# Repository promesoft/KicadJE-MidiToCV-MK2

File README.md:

# Kicad-MidiToCV
Midi to CV in Eurorack 

# MK2 Design 
## Status - PCB delivered tested
## Initial 
| Stage  | Detail | Status |
| ------------- | ------------- | ------------- |
| create material  | sch/pcb | produced MK2 Rev A  |
| | gerber | Produced MK2 |
| production  | ordered  |  |
|  | produced | yes |
|  | delivered | yes |
## Preliminary validation
| Test  | Detail | Status |
| ------------- | ------------- | ------------- |
| Initial Inspection | conflict between LED on front panel and optional CV7 | OK |
| Initial Technical Test |   | OK |
| Initial Product Test |  | OK! |
|  | LED's | OK |
|  | Encoder | OK |
|  | CV1+CV2 | OK |
|  | GATE 1,2,3,4 | OK |
|  | MIDI I/O | OK |

## Secondary validation
| Test  | Detail | Status |
| ------------- | ------------- |------------- |
| Product Test |  | |
| Quality |  | |
| Long Term Product Test | | Mounted in rack |

## Software 
| Test  | Detail | Status |
| ------------- | ------------- |------------- |
| Initial SW | copy from MK1 and adjusted | OK! |
| MIDI I/O | UI | |
| MIDI I/O | Filtering and change ch | |
| CV Control | UI |  |
| CV Control | |  |
| LFO Control | UI |  |
| LFO Control | Function |  |

## Errata
 * Physical mounting of the faceplate to holes on the base plate requires other dimensions of the angled mounts. The mounts can be very difficult to get in place due to limited space behind the front PCB.
## Issues and Notes
 * Note - the 4 value LED's are routed across the front board next to analogue and gate signals - so care should be taken when deciding between constant power or PWM control of brightness. The other LED's are not considered as vital as they will normally be lit when config is changed.
 * Consider replacing single row board connector with double row.
 * Physical construction not finalized
### Workarounds

## Base Construction
### Arduino base board 
 - Arduino Nano
 - MIDI IN/OUT connectors
 - CV 1 and CV 2 as Mini Jacks (PJ-301) with variable x2-x3 amplification and 1st order LP filter
 - Gate 1 and Gate 2 as Mini Jacks (PJ-301) 5V
 - Gate 3 and Gate 4 as Mini Jacks (PJ-321) with fixed x2 amplification and sallen-key LP 2nd order filter
 - Board connector 9pin and 11pin from base board to front board
 - 16pin Europower connector
 - Barreljack for 7-12V digital Pwr

## Vital Components
 - Arduino Nano - where the magic lives (remember to socket it to be able to reprogram it - two jumpers are in place for Rx/Tx so socket may be avoided)
 - Jack connectors: PJ-321 for the base board and PJ-301 for the front board (important for the footprint)
 - ALPS EC-11 Encoder (important for the footprint and 3D alignment)
 - ALPS RV09 horisontal potentiometer (important for the footprint and for variable CV out - can be omitted if this is not needed)
 - MCP4825 module - if chosen (important for CV out function - footprint needs to match)
 - TL072 or similar dual op amp
 
### Mechanical

The construction is still split in two - but the MK2 design relies on a base board that is 90degrees to the face plate (like the MK1) and a connector board that is 10mm behind the faceplate 90 degrees angle to the base board.

.png)
-----------------------------------------------------

# MK1 Design
## Status - Rev B - Ongoing PCB layout and Sch update

## Status - Rev A Mounted - Midi code in progress
### Issues and Notes
Please note that the PIN1 and PIN2 are GATE. This is note described clearly in http://www.doepfer.de/a100_man/a100t_e.htm and needs to be noted when soldering the IDC header or when cabling if a Pin header has been mounted.
 * The two pots on the breakout board are too close for adding a knob
 * The orientation of the pinheader for the MCP4725 module - if mounted incorrectly the magic smoke disappears
 * 0R could be replaced with SMD jumpers
 * Consider a 200 mA fuse for Vin and 50mA for +5V pwr
 * The mounting hole that is off center is not matching both boards
### Errata
 * Footprint of PJ-321 has too small drill holes (1mm) - major
 * Footprint of PJ-321 is too narrow in the rear end :) - minor issue
 * Midi out circuit is WRONG - Major
### Workarounds
* Midi out not working - PCB workaround mod partially possible  
 * --Remove GND around DIN pin 5 (bottom copper side)
 * --Cut GND track to DIN pin 5 (top copper side)
 * --Remove Q1, R6, R9
 * --Connect 220R THT to base pad on Q1
 * --Connect C and E on Q1
 * --Add GND wire to pin2 of MIDI out DIN
## Physical Construction
 - 100x100mm
 - Separate unit with no alteration
 - Optional split in 2 for eurorack mount mirrored config

## Vital Components
 - Arduino Nano - where the magic lives (remember to socket it to be able to reprogram it)
 - Jack connectors: PJ-321 (important for the footprint)
 - KY-40 Encoder module (important for the pullup, footprint and 3D alignment)
 - MCP4825 module - if chosen (important for CV out function - footprint needs to match)
 If these are chosen the last two CV jacks should be ommitted.
 - MCP4728 chip - if chosen (important for the last 2 CV out)

## MIDI Board Features
### Single board - MIDI I/O and MIDI to CV
The board can be used as is for a prototype development of MIDI to CV
### Split board Eurorack - MIDI I/O and MIDI to CV
The board can be devided in two and combined front to front with spacers for a MIDI to CV eurorack module.
### Base board Eurorack - MIDI I/O
If only MIDI features are required the base board can work without the IO section.

## Generic Board Features
### Split board Options
The main board (with the arduino) has a couple of headers that can be connected to a different interface board using I2C, Analogue Inputs and Digital I/O.
### Non MIDI board
The MIDI components can be omitted if the features does not require MIDI, like an LFO, VCO or ADSR circuit.

## Base Construction
Arduino Nano based Controller and MIDI decoder.

### MIDI In
MIDI In through a PC814 (or optional PC817) Optocoupler and into the RX pin on the Arduino

### Midi Out
Optional expansion

### Gate
Gate pins from Arduino

## CV Out
I2C Dac with 2 options
### I2C Dac - Option 1 - Two Single channel DAC
2x MCP4725 DAC 
### I2C Dac - Option 2 - One 4 channel DAC
1x MCP4728

# RevB

# RevA

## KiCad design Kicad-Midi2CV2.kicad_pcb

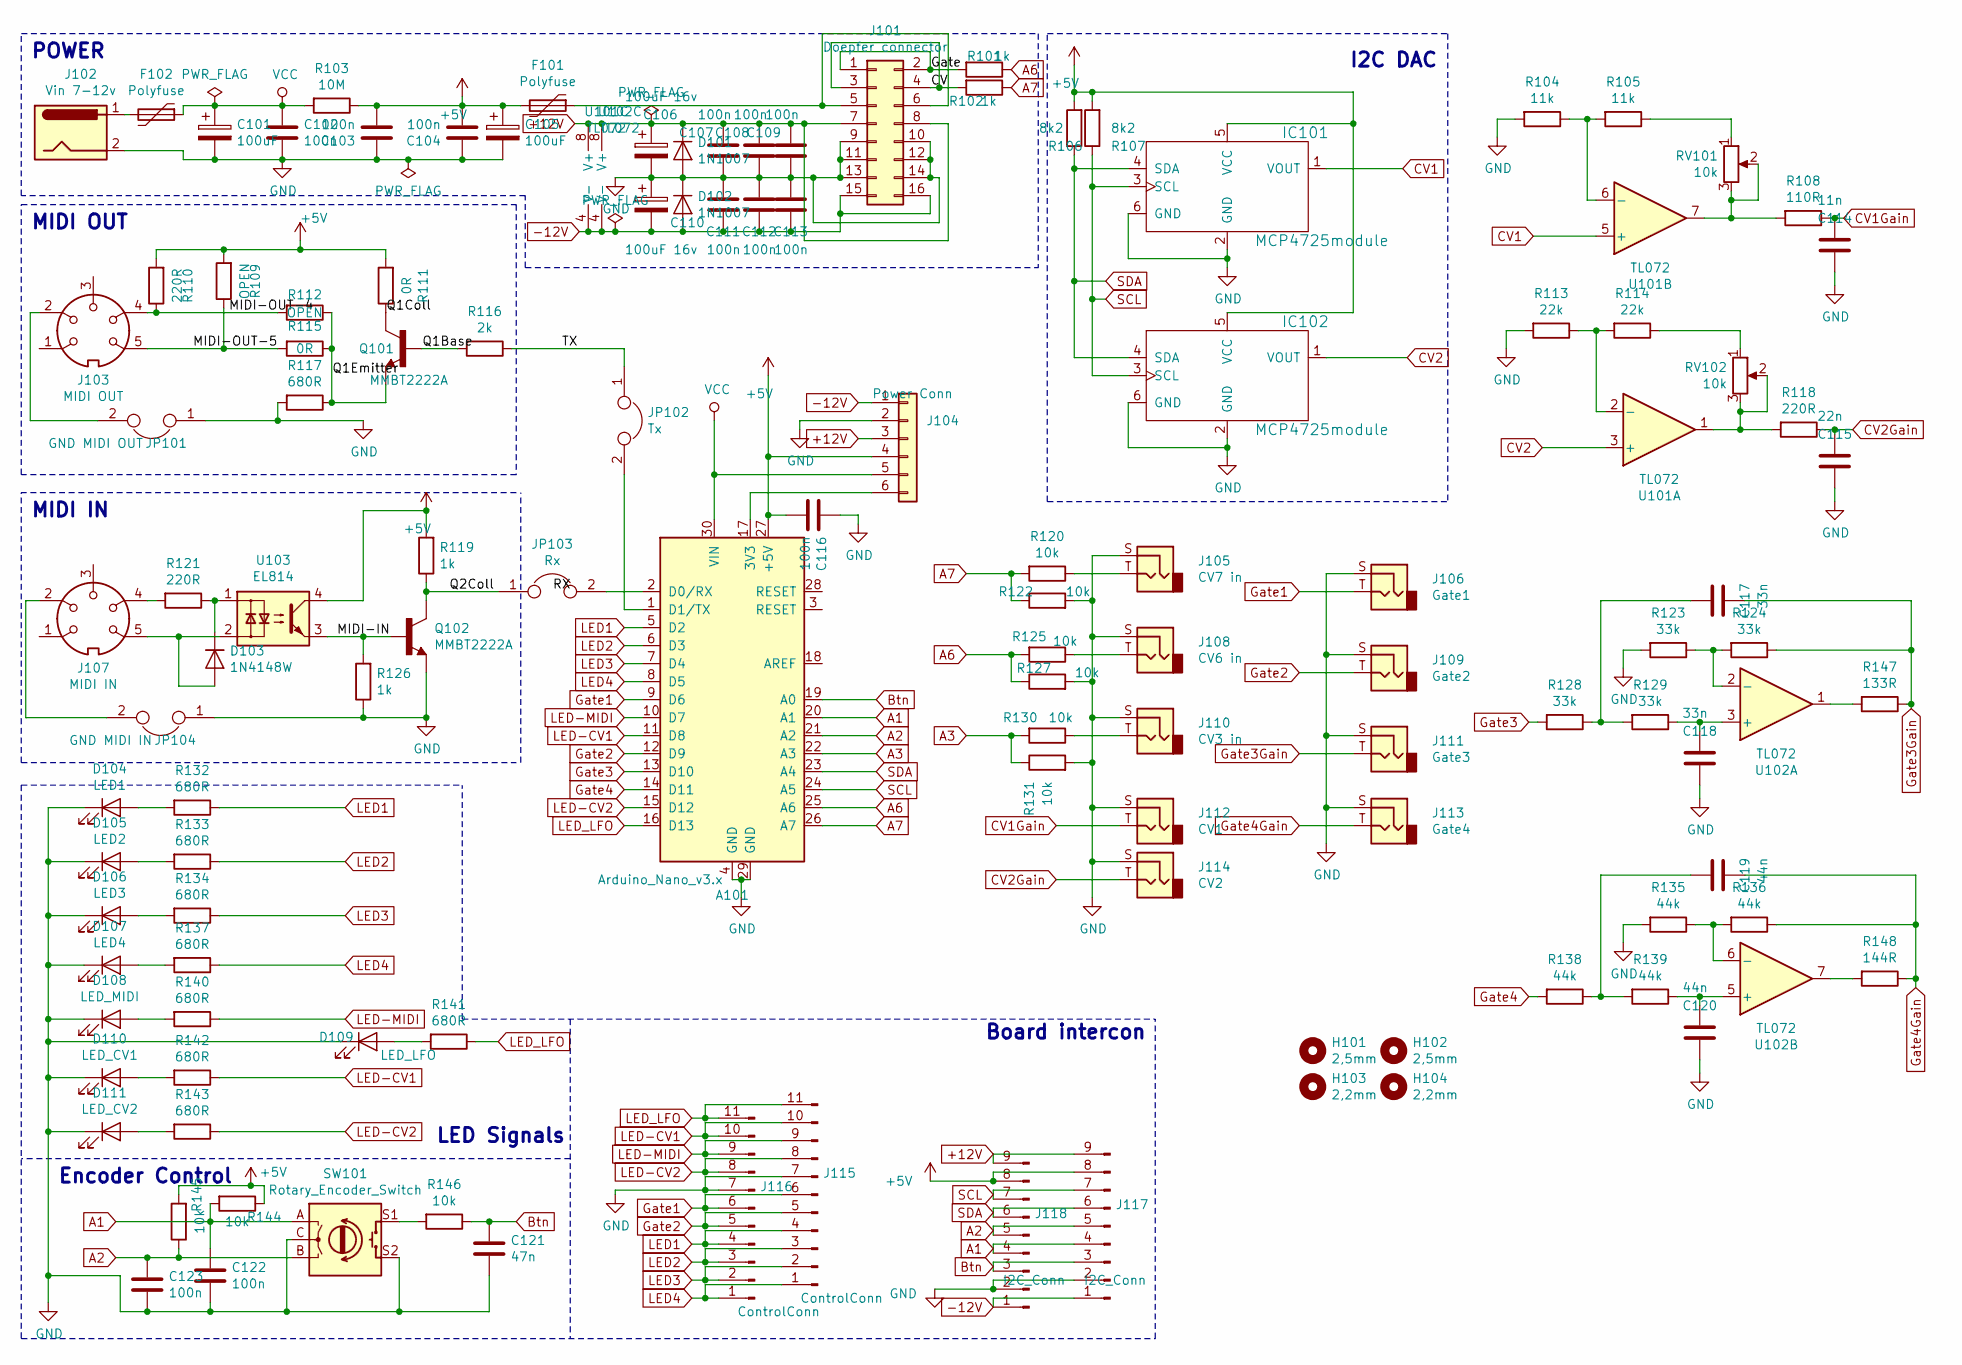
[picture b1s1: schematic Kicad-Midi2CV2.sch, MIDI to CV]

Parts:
A101: Arduino_Nano_v3.x; Arduino_Nano
C101, C105: 100uF; CP_Radial_D5.0mm_P2.50mm
C102, C103, C104, C107, C108, C109, C111, C112, C113, C116, C122, C123: 100n; C_0805_2012Metric_Pad1.15x1.40mm_HandSolder
C106, C110: 100uF 16v; CP_Radial_D5.0mm_P2.50mm
C114: 11n; C_0805_2012Metric_Pad1.15x1.40mm_HandSolder
C115: 22n; C_0805_2012Metric_Pad1.15x1.40mm_HandSolder
C117, C118: 33n; C_0805_2012Metric_Pad1.15x1.40mm_HandSolder
C119, C120: 44n; C_0805_2012Metric_Pad1.15x1.40mm_HandSolder
C121: 47n; C_0805_2012Metric_Pad1.15x1.40mm_HandSolder
D101, D102: 1N1007; D_SOD-123
D103: 1N4148W; D_SOD-123
D104: LED1; LED_D3.0mm
D105: LED2; LED_D3.0mm
D106: LED3; LED_D3.0mm
D107: LED4; LED_D3.0mm
D108: LED_MIDI; LED_D3.0mm
D109: LED_LFO; LED_D3.0mm
D110: LED_CV1; LED_D3.0mm
D111: LED_CV2; LED_D3.0mm
F101, F102: Polyfuse; Fuse_1206_3216Metric_Pad1.42x1.75mm_HandSolder
H101, H102: 2,5mm; MountingHole_2.5mm_Pad_Via
H103: 2,2mm; MountingHole_2.5mm_Pad_Via
H104: 2,2mm; MountingHole_2.2mm_M2_Pad_Via
IC101, IC102: MCP4725module; PinSocket_1x06_P2.54mm_Vertical
J101: Doepfer connector; PinSocket_2x08_P2.54mm_Vertical
J102: Vin 7-12v; BarrelJack_CUI_PJ-063AH_Horizontal
J103: MIDI OUT; din-5
J104: Power Conn; PinHeader_1x06_P2.54mm_Vertical
J105: CV7 in; AudioJack3StereoNarrow-PJ-321
J106: Gate1; PJ301SM
J107: MIDI IN; din-5
J108: CV6 in; AudioJack3StereoNarrow-PJ-321
J109: Gate2; PJ301SM
J110: CV3 in; AudioJack3StereoNarrow-PJ-321
J111: Gate3; AudioJack3StereoNarrow-PJ-321
J112: CV1; PJ301SM
J113: Gate4; AudioJack3StereoNarrow-PJ-321
J114: CV2; PJ301SM
J115, J116: ControlConn; PinHeader_1x11_P2.54mm_Vertical
J117, J118: I2C_Conn; PinHeader_1x09_P2.54mm_Vertical
JP101: GND MIDI OUT; SolderJumper-2_P1.3mm_Bridged_RoundedPad1.0x1.5mm
JP102: Tx; PinSocket_1x02_P2.54mm_Vertical
JP103: Rx; PinSocket_1x02_P2.54mm_Vertical
JP104: GND MIDI IN; SolderJumper-2_P1.3mm_Open_RoundedPad1.0x1.5mm
Q101, Q102: MMBT2222A; SOT-23_Handsoldering
R101, R102, R119, R126: 1k; R_0805_2012Metric_Pad1.15x1.40mm_HandSolder
R103: 10M; R_0805_2012Metric_Pad1.15x1.40mm_HandSolder
R104, R105: 11k; R_0805_2012Metric_Pad1.15x1.40mm_HandSolder
R106, R107: 8k2; R_0805_2012Metric_Pad1.15x1.40mm_HandSolder
R108: 110R; R_0805_2012Metric_Pad1.15x1.40mm_HandSolder
R109, R112: OPEN; R_0805_2012Metric_Pad1.15x1.40mm_HandSolder
R110, R118, R121: 220R; R_0805_2012Metric_Pad1.15x1.40mm_HandSolder
R111, R115: 0R; SolderJumper-2_P1.3mm_Bridged_RoundedPad1.0x1.5mm
R113, R114: 22k; R_0805_2012Metric_Pad1.15x1.40mm_HandSolder
R116: 2k; R_0805_2012Metric_Pad1.15x1.40mm_HandSolder
R117, R132, R133, R134, R137, R140, R141, R142, R143: 680R; R_0805_2012Metric_Pad1.15x1.40mm_HandSolder
R120, R122, R125, R127, R130, R131, R144, R145, R146: 10k; R_0805_2012Metric_Pad1.15x1.40mm_HandSolder
R123, R124, R128, R129: 33k; R_0805_2012Metric_Pad1.15x1.40mm_HandSolder
R135, R136, R138, R139: 44k; R_0805_2012Metric_Pad1.15x1.40mm_HandSolder
R147: 133R; R_0805_2012Metric_Pad1.15x1.40mm_HandSolder
R148: 144R; R_0805_2012Metric_Pad1.15x1.40mm_HandSolder
RV101, RV102: 10k; Potentiometer_Alps_RK09K_Single_Vertical
SW101: Rotary_Encoder_Switch; RotaryEncoder_Alps_EC11E-Switch_Vertical_H20mm
U101, U102: TL072; AJ_SO-8_5.3x6.2mm_P1.27mm
U103: EL814; DIP-4_W7.62mm_LongPads

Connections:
+5V: A101.27 (+5V), C103.2, C104.2, C105.1, C116.2, F101.2, IC101.5 (VCC), IC102.5 (VCC), J104.4, J117.8, J118.8, R103.1, R106.2, R107.2, R109.2, R110.2, R111.2, R119.2, R144.1, R145.2, U103.4
+12V: C106.1, C107.2, C108.2, C109.2, D101.1 (K), J101.7, J101.8, J104.3, J117.9, J118.9, U101.8 (V+), U102.8 (V+)
-12V: C110.2, C111.1, C112.1, C113.1, D102.2 (A), J101.15, J101.16, J104.1, J117.1, J118.1, U101.4 (V-), U102.4 (V-)
/CV: J101.3, J101.4, R102.2
/Gate: J101.1, J101.2, R101.2
/MIDI-IN: Q102.1 (B), R126.2, U103.3
/MIDI-OUT-4: J103.4, R110.1, R112.2
/MIDI-OUT-5: J103.5, R109.1, R115.2
/Q1Base: Q101.1 (B), R116.2
/Q1Coll: Q101.3 (C), R111.1
/Q1Emitter: Q101.2 (E), R112.1, R115.1, R117.1
/Q2Coll: JP103.1, Q102.3 (C), R119.1
/TX: JP102.1, R116.1
A1: A101.20 (A1), C122.1, J117.4, J118.4, R144.2, SW101.A
A2: A101.21 (A2), C123.1, J117.5, J118.5, R145.1, SW101.B
A3: A101.22 (A3), R130.2, R131.1
A6: A101.25 (A6), R101.1, R125.2, R127.1
A7: A101.26 (A7), R102.1, R120.2, R122.1
Btn: A101.19 (A0), C121.1, J117.3, J118.3, R146.1
CV1: IC101.1 (VOUT), U101.5 (+)
CV1Gain: C114.1, J112.T, R108.1
CV2: IC102.1 (VOUT), U101.3 (+)
CV2Gain: C115.1, J114.T, R118.1
GND: A101.4 (GND), A101.29 (GND), C101.2, C102.2, C103.1, C104.1, C105.2, C106.2, C107.1, C108.1, C109.1, C110.1, C111.2, C112.2, C113.2, C114.2, C115.2, C116.1, C118.2, C120.2, C121.2, C122.2, C123.2, D101.2 (A), D102.1 (K), D104.1 (K), D105.1 (K), D106.1 (K), D107.1 (K), D108.1 (K), D109.1 (K), D110.1 (K), D111.1 (K), IC101.2 (GND), IC101.6 (GND), IC102.2 (GND), IC102.6 (GND), J101.9, J101.10, J101.11, J101.12, J101.13, J101.14, J102.2, J104.2, J105.S, J106.S, J108.S, J109.S, J110.S, J111.S, J112.S, J113.S, J114.S, J115.7, J116.7, J117.2, J118.2, JP101.1, JP104.1, Q102.2 (E), R104.2, R113.2, R117.2, R122.2, R123.2, R126.1, R127.2, R131.2, R135.2, SW101.C, SW101.S2
Gate1: A101.9 (D6), J106.T, J115.6, J116.6
Gate2: A101.12 (D9), J109.T, J115.5, J116.5
Gate3: A101.13 (D10), R128.2
Gate3Gain: C117.1, J111.T, R124.1, R147.1
Gate4: A101.14 (D11), R138.2
Gate4Gain: C119.1, J113.T, R136.1, R148.1
LED1: A101.5 (D2), J115.4, J116.4, R132.1
LED2: A101.6 (D3), J115.3, J116.3, R133.1
LED3: A101.7 (D4), J115.2, J116.2, R134.1
LED4: A101.8 (D5), J115.1, J116.1, R137.1
LED-CV1: A101.11 (D8), J115.10, J116.10, R142.1
LED-CV2: A101.15 (D12), J115.8, J116.8, R143.1
LED-MIDI: A101.10 (D7), J115.9, J116.9, R140.1
LED_LFO: A101.16 (D13), J115.11, J116.11, R141.1
unnamed: A101.1 (D1/TX), JP102.2
unnamed: A101.2 (D0/RX), JP103.2
unnamed: A101.17 (3V3), J104.6
unnamed: C117.2, R128.1, R129.2
unnamed: C118.1, R129.1, U102.3 (+)
unnamed: C119.2, R138.1, R139.2
unnamed: C120.1, R139.1, U102.5 (+)
unnamed: D103.1 (K), R121.1, U103.1
unnamed: D103.2 (A), J107.5, U103.2
unnamed: D104.2 (A), R132.2
unnamed: D105.2 (A), R133.2
unnamed: D106.2 (A), R134.2
unnamed: D107.2 (A), R137.2
unnamed: D108.2 (A), R140.2
unnamed: D109.2 (A), R141.2
unnamed: D110.2 (A), R142.2
unnamed: D111.2 (A), R143.2
unnamed: F101.1, J101.5, J101.6
unnamed: F102.2, J102.1
unnamed: J103.2, JP101.2
unnamed: J105.T, R120.1
unnamed: J107.2, JP104.2
unnamed: J107.4, R121.2
unnamed: J108.T, R125.1
unnamed: J110.T, R130.1
unnamed: R104.1, R105.2, U101.6 (-)
unnamed: R105.1, RV101.1
unnamed: R108.2, RV101.2, RV101.3, U101.7
unnamed: R113.1, R114.2, U101.2 (-)
unnamed: R114.1, RV102.1
unnamed: R118.2, RV102.2, RV102.3, U101.1
unnamed: R123.1, R124.2, U102.2 (-)
unnamed: R135.1, R136.2, U102.6 (-)
unnamed: R146.2, SW101.S1
unnamed: R147.2, U102.1
unnamed: R148.2, U102.7
SCL: A101.24 (A5), IC101.3 (SCL), IC102.3 (SCL), J117.7, J118.7, R107.1
SDA: A101.23 (A4), IC101.4 (SDA), IC102.4 (SDA), J117.6, J118.6, R106.1
VCC: A101.30 (VIN), C101.1, C102.1, F102.1, J104.5, R103.2

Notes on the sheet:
MIDI IN
LED Signals
Encoder Control
I2C DAC
POWER
MIDI OUT
Board intercon

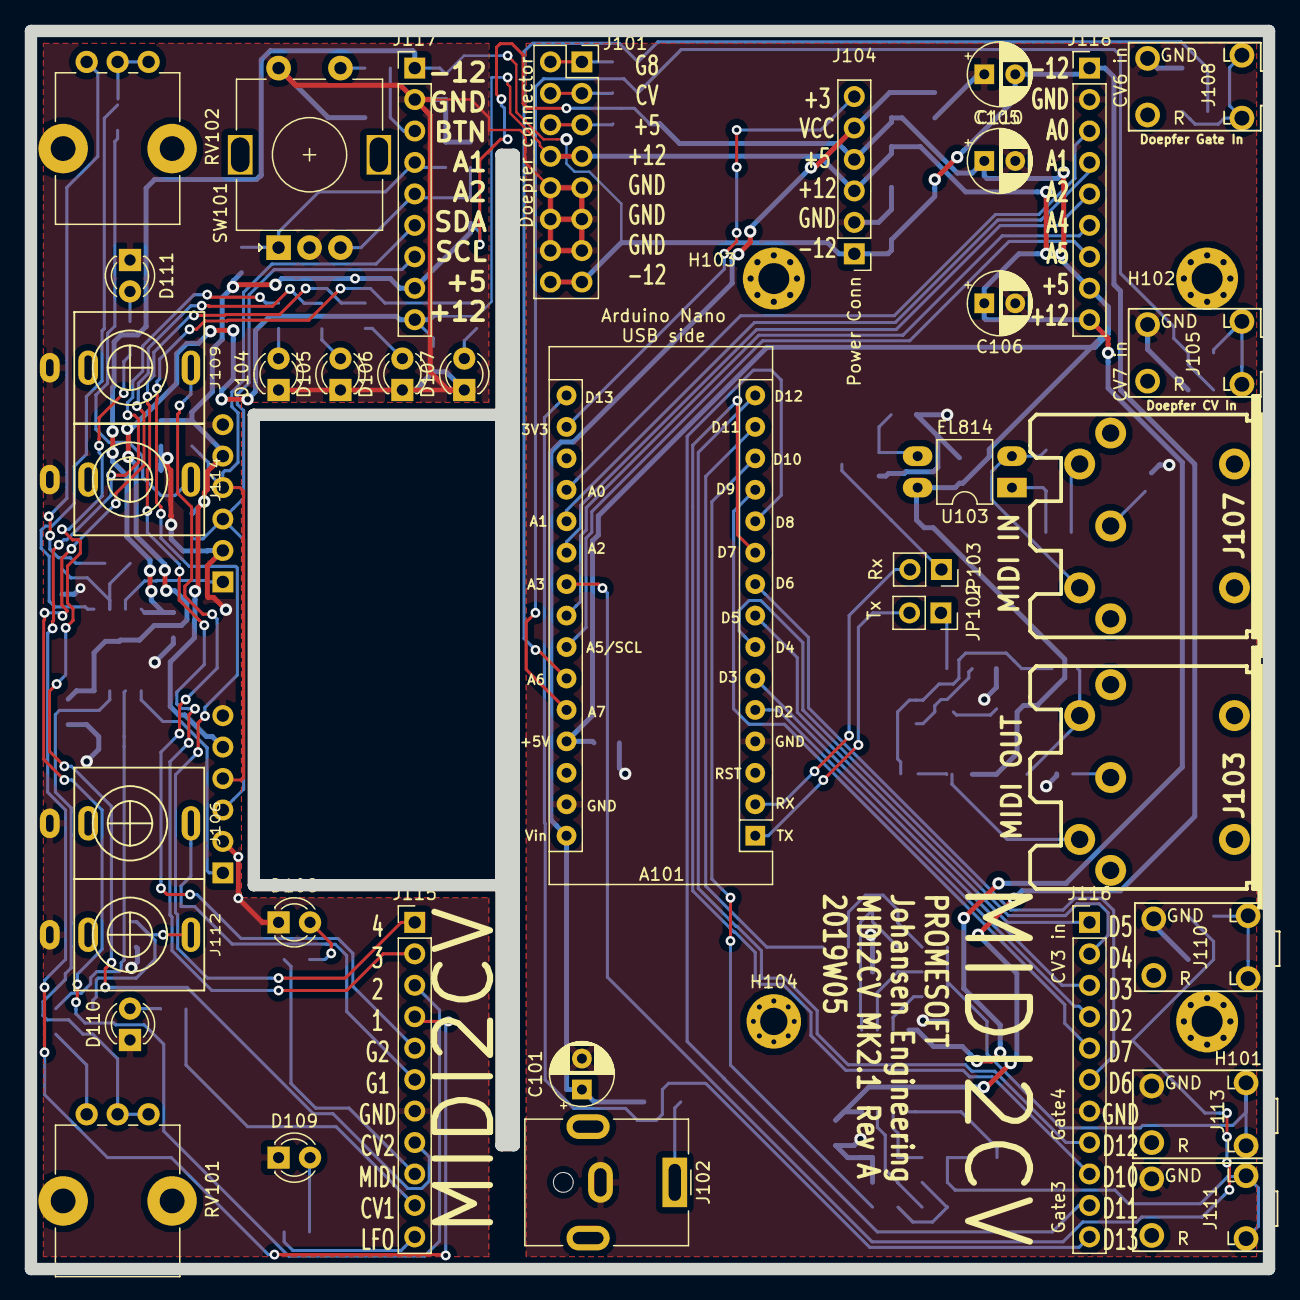
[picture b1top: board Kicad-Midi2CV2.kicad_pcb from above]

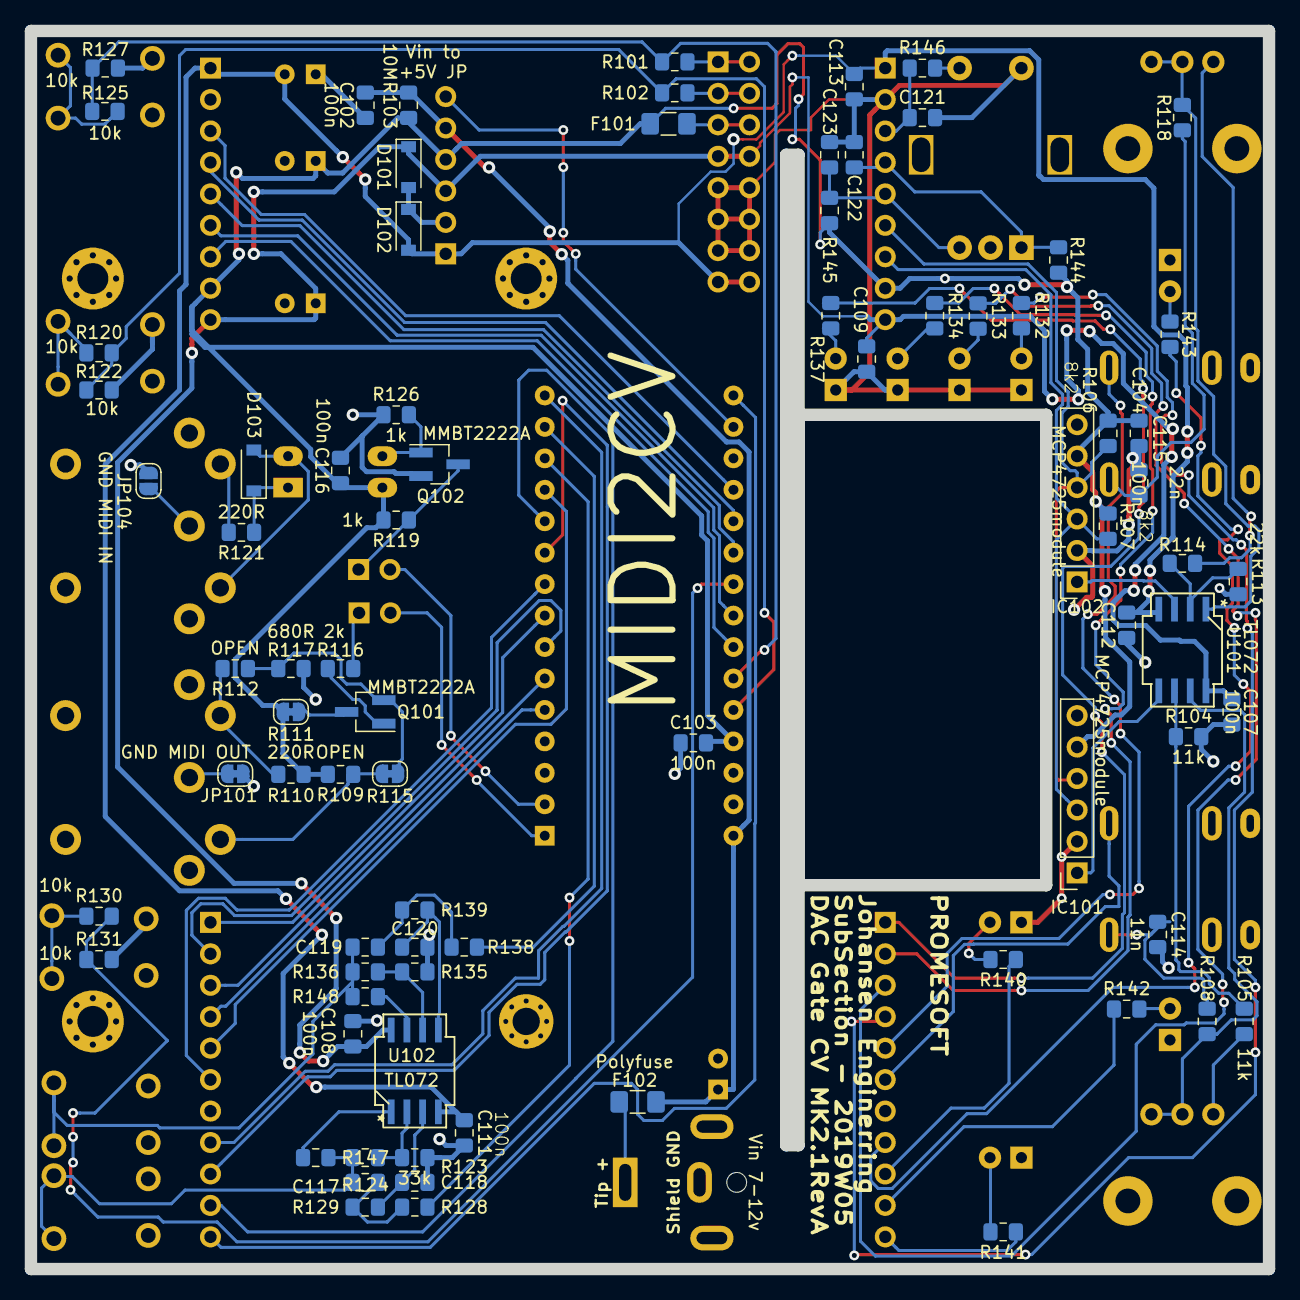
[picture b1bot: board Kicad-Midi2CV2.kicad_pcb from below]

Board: 2 copper layers, 100.0 x 100.0 mm, 121 parts (80 on the bottom side), 77 nets.

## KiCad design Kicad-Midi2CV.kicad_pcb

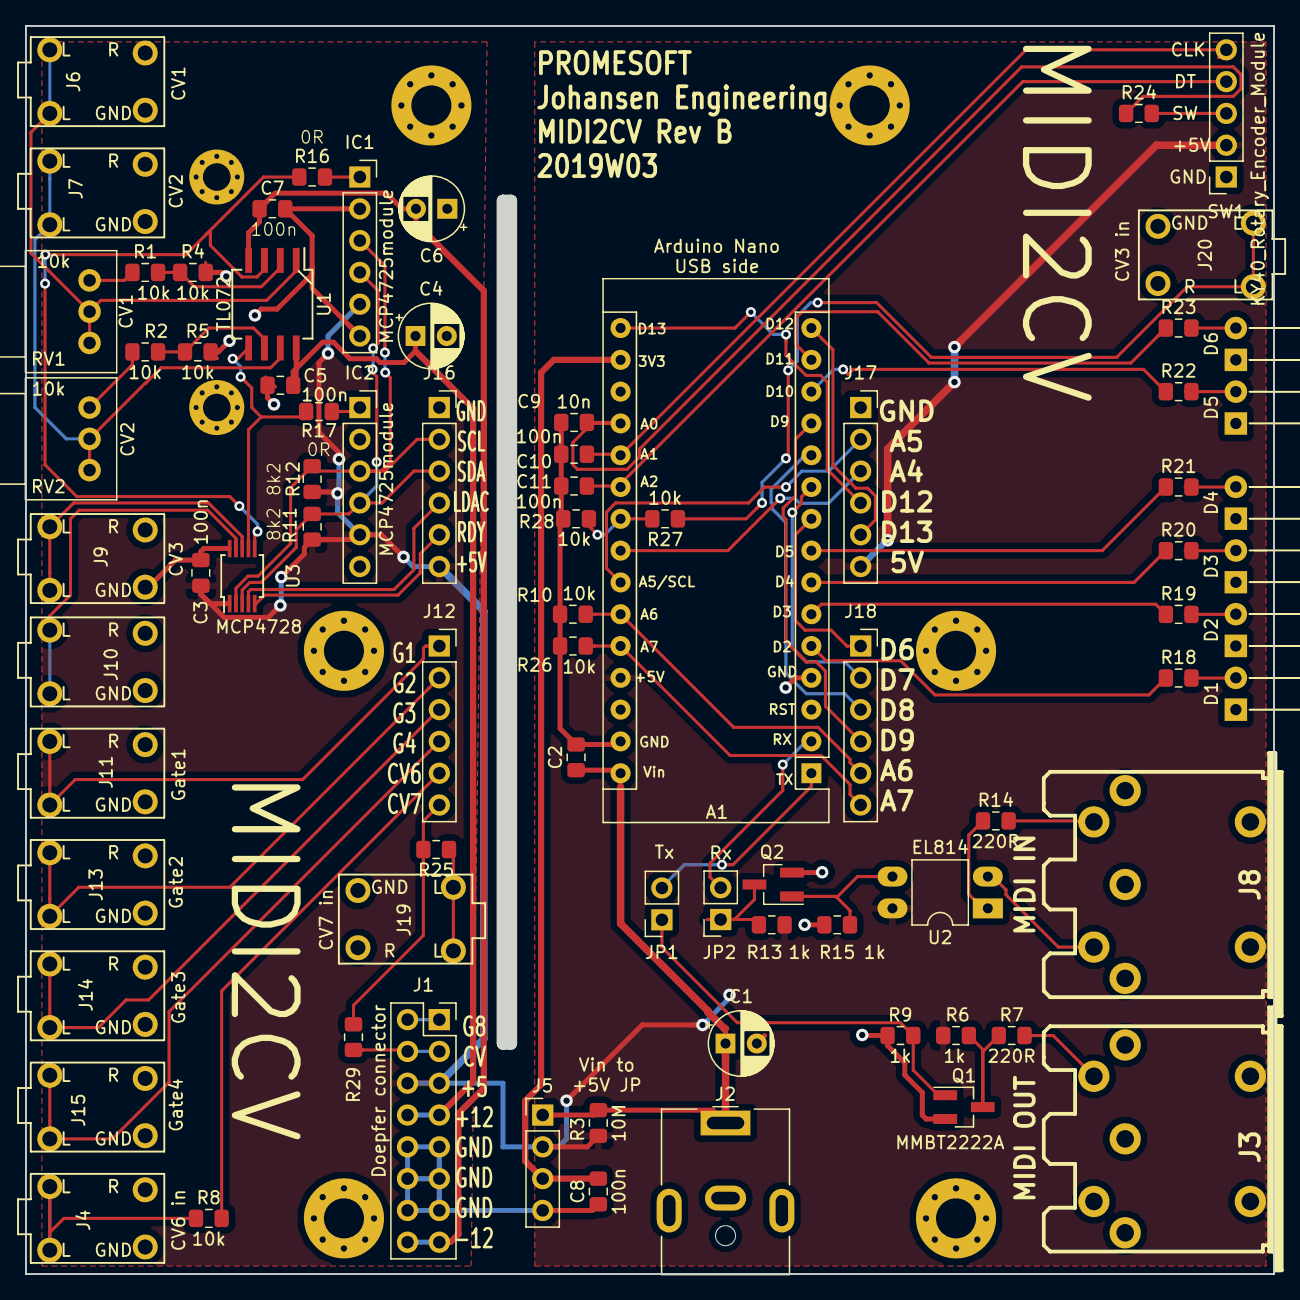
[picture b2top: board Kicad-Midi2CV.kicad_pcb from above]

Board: 2 copper layers, 98.8 x 98.8 mm, 79 parts (0 on the bottom side), 60 nets.

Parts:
A1: Arduino_Nano_v3.x; Arduino_Nano
C1: 100uF; CP_Radial_D5.0mm_P2.50mm
C2, C3, C5, C7, C8, C10, C11: 100n; C_0805_2012Metric_Pad1.15x1.40mm_HandSolder
C4, C6: 100uF 16v; CP_Radial_D5.0mm_P2.50mm
C9: 10n; C_0805_2012Metric_Pad1.15x1.40mm_HandSolder
D1: LED1; LED_D3.0mm_Horizontal_O6.35mm_Z6.0mm
D2: LED2; LED_D3.0mm_Horizontal_O6.35mm_Z6.0mm
D3: LED3; LED_D3.0mm_Horizontal_O6.35mm_Z6.0mm
D4: LED4; LED_D3.0mm_Horizontal_O6.35mm_Z6.0mm
D5: LEDset1; LED_D3.0mm_Horizontal_O6.35mm_Z6.0mm
D6: LEDset2; LED_D3.0mm_Horizontal_O6.35mm_Z6.0mm
IC1, IC2: MCP4725module; PinSocket_1x06_P2.54mm_Vertical
J1: Doepfer connector; PinSocket_2x08_P2.54mm_Vertical
J2: Vin 7-12v; BarrelJack_CUI_PJ-063AH_Horizontal
J3: MIDI OUT; din-5
J4: CV6 in; AudioJack3StereoNarrow-PJ-321
J5: Power Conn; PinHeader_1x04_P2.54mm_Vertical
J6: CV1; AudioJack3StereoNarrow-PJ-321
J7: CV2; AudioJack3StereoNarrow-PJ-321
J8: MIDI IN; din-5
J9: CV3; AudioJack3StereoNarrow-PJ-321
J10: CV4; AudioJack3StereoNarrow-PJ-321
J11: Gate1; AudioJack3StereoNarrow-PJ-321
J12, J18: GateConn; PinSocket_1x06_P2.54mm_Vertical
J13: Gate2; AudioJack3StereoNarrow-PJ-321
J14: Gate3; AudioJack3StereoNarrow-PJ-321
J15: Gate4; AudioJack3StereoNarrow-PJ-321
J16, J17: I2C_Conn; PinSocket_1x06_P2.54mm_Vertical
J19: CV7 in; AudioJack3StereoNarrow-PJ-321
J20: CV3 in; AudioJack3StereoNarrow-PJ-321
JP1: Tx; PinSocket_1x02_P2.54mm_Vertical
JP2: Rx; PinSocket_1x02_P2.54mm_Vertical
Q1, Q2: MMBT2222A; SOT-23_Handsoldering
R1, R2, R4, R5, R8, R10, R24, R25, R26, R27, R28: 10k; R_0805_2012Metric_Pad1.15x1.40mm_HandSolder
R3: 10M; R_0805_2012Metric_Pad1.15x1.40mm_HandSolder
R6, R9, R13, R15, R29: 1k; R_0805_2012Metric_Pad1.15x1.40mm_HandSolder
R7, R14: 220R; R_0805_2012Metric_Pad1.15x1.40mm_HandSolder
R11, R12: 8k2; R_0805_2012Metric_Pad1.15x1.40mm_HandSolder
R16, R17: 0R; R_0805_2012Metric_Pad1.15x1.40mm_HandSolder
R18, R19, R20, R21, R22, R23: 680R; R_0805_2012Metric_Pad1.15x1.40mm_HandSolder
RV1, RV2: 10k; Potentiometer_Alps_RK097_Single_Horizontal
SW1: KY40_Rotary_Encoder_Module; KY-40-rotary-encoder-board
U1: TL072; AJ_SO-8_5.3x6.2mm_P1.27mm
U2: EL814; DIP-4_W7.62mm_LongPads
U3: MCP4728; MSOP-10_3x3mm_P0.5mm

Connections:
+5V: A1.27, C3.2, IC1.5, IC2.5, J1.5, J1.6, J5.2, J16.6, J17.6, R3.1, R6.2, R11.2, R12.2, R13.2, SW1.5V, U2.4, U3.1
/12v: C4.1, C5.2, J1.7, J1.8, U1.8
/-12v: C6.2, C7.1, J1.15, J1.16, U1.4
/CV: J1.3, J1.4, R29.2
/Gate: J1.1, J1.2
/LDAC: A1.16, J16.4, J17.4, U3.4
/MIDI-IN: Q2.1, R15.2, U2.3
/MIDI-OUT: Q1.3, R6.1, R7.1
/RDY-BSY: A1.15, J16.5, J17.5, U3.5
/SCL: A1.24, IC1.3, IC2.3, J16.2, J17.2, R12.1, U3.2
/SDA: A1.23, IC1.4, IC2.4, J16.3, J17.3, R11.1, U3.3
/TX: JP1.1, Q1.1, R9.2
/Vout1: IC1.1, R16.2
/Vout2: IC2.1, R17.2
A1: A1.20, C10.1, SW1.CLK
A2: A1.21, C11.1, SW1.DT
A3: A1.22, R27.2, R28.1
A6: A1.25, J12.5, J18.5, R8.2, R10.1
A7: A1.26, J12.6, J18.6, R25.2, R26.1, R29.1
Btn: A1.19, C9.1, R24.1
CV1: R16.1, U1.3, U3.6
CV1Gain: J6.T, RV1.2, RV1.3, U1.1
CV2: R17.1, U1.5, U3.7
CV2Gain: J7.T, RV2.2, RV2.3, U1.7
CV3: J9.T, U3.8
CV4: J10.T, U3.9
GND: A1.4, A1.29, C1.2, C2.2, C3.1, C4.2, C5.1, C6.1, C7.2, C8.1, C9.2, C10.2, C11.2, D1.1, D2.1, D3.1, D4.1, D5.1, D6.1, IC1.2, IC1.6, IC2.2, IC2.6, J1.9, J1.10, J1.11, J1.12, J1.13, J1.14, J2.2, J3.5, J4.S, J5.4, J6.S, J7.S, J9.S, J10.S, J11.S, J13.S, J14.S, J15.S, J16.1, J17.1, J19.S, J20.S, Q1.2, Q2.2, R4.2, R5.2, R9.1, R10.2, R15.1, R26.2, R28.2, SW1.GND, U3.10
Gate1: A1.9, J11.T, J12.1, J18.1
Gate2: A1.10, J12.2, J13.T, J18.2
Gate3: A1.11, J12.3, J14.T, J18.3
Gate4: A1.12, J12.4, J15.T, J18.4
LED1: A1.5, R18.1
LED2: A1.6, R19.1
LED3: A1.7, R20.1
LED4: A1.8, R21.1
LED-sel: A1.13, R22.1
LED-sel2: A1.14, R23.1
unnamed: A1.1, JP1.2
unnamed: A1.2, JP2.2
unnamed: A1.17, C8.2, J5.3
unnamed: D1.2, R18.2
unnamed: D2.2, R19.2
unnamed: D3.2, R20.2
unnamed: D4.2, R21.2
unnamed: D5.2, R22.2
unnamed: D6.2, R23.2
unnamed: J3.4, R7.2
unnamed: J4.T, R8.1
unnamed: J8.4, R14.2
unnamed: J8.5, U2.2
unnamed: J19.T, R25.1
unnamed: J20.T, R27.1
unnamed: JP2.1, Q2.3, R13.1
unnamed: R1.1, RV1.1
unnamed: R1.2, R4.1, U1.2
unnamed: R2.1, RV2.1
unnamed: R2.2, R5.1, U1.6
unnamed: R14.1, U2.1
unnamed: R24.2, SW1.SW
VCC: A1.30, C1.1, C2.1, J2.1, J5.1, R3.2

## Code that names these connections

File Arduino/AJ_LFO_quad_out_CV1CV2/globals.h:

#include <EEPROM.h>
#include <Adafruit_MCP4725.h>
/* -----------------------------------------------
 *  GLOBAL DEFINES
 * -----------------------------------------------
 */
//OVERRIDE PINS FOR LFO
#define PWM1 10 // Sets Pin PWM1 PWM-Output = Gate 3
#define PWM2 11 // Sets Pin PWM2 PWM-Output = Gate 4

//OVERRIDE PIN FOR SQUARE LFO
#define Square 9    //  Pin as LED for Tempo LED and as a square-LFO 
#define InvSquare 6 //  Pin as LED for Tempo LED and as a inverted square-LFO 

#define SWpin A0 //add 100nF to GND for debounce 
#define Apin A1 //add 100nF to GND for debounce
#define Bpin A2 //add 100nF to GND for debounce
#define CV3in A3 // Base board
#define SDA A4 // Addon board
#define SCL A5 // Addon board
#define CV6in A6 // Doepfer Gate in + Base board
#define CV7in A7 // Doepfer CV in + Base board

#define LED1 2
#define LED2 3
#define LED3 4
#define LED4 5
#define LED_MIDI 7
#define LED_CV1 8
#define LED_CV2 12
#define LED_LFO 13

#define Gate1 6 // Addon board
#define Gate2 9 // Addon board
#define Gate3 10 // Base board
#define Gate4 11 // Base board

//#define RDY-BSY 12
//#define LDAC 13

#define MCP4725_ADDR 0x60   
#define MCP4725_ADDR2 0x61   
/* -----------------------------------------------
 *  GLOBAL VAR
 * -----------------------------------------------
 */
boolean A_old=0, B_old=1, SW_old=0;
boolean left = false, right = false, button = false;

//Structure for keeping MIDI CH data for LED
boolean LEDData[4][4]; //(see state)

boolean LEDSelData = false, LEDSel2Data = false; 
unsigned int encoder[4], buttoncnt = 0;
unsigned int state = 0; 
//For MIDI In/Out/CV - State 00 = MidiDataInChannel - 01 = MIDI CH in select - 10 = MIDI CH OUT select - 11 = MIDI CH 2 CV select
//For MIDI In/CV/LFO - State 00 = MIDI CH 1 CV select - 01 = MIDI CH 2 CV select - 10 = LFO Waveform - 11 = LFO Speed

//byte midi_channel=4;
//Structure for keeping MIDI CH data for processing
//With LFO state 0 and 1 are reserved for CV MIDI channels
//With LFO state 2 and 3 are reserved for the LFO settings
byte MIDI_CH[4]; //(see state above)

unsigned long lastwaveupdate = 0; // LFO millis timer between samples
//unsigned int PWMshape = 0;
unsigned int delayTime = 4; 
uint8_t tableStep = 0;
uint8_t PWMdata = 0;

/* -----------------------------------------------
 *  MIDI2CV VAR
 * -----------------------------------------------
 */
Adafruit_MCP4725 dac;
Adafruit_MCP4725 dac2;
 
int pitches[61] = 
{
     0,   70,  142,  214,  286,  358,  419,  500, 
   571,  642,  713,  786,  860,  933, 1006, 1080, 
  1153, 1226, 1299, 1372, 1445, 1518, 1591, 1664, 
  1737, 1808, 1880, 1952, 2024, 2096, 2168, 2240,
  2310, 2380, 2452, 2525, 2600, 2670, 2740, 2810,
  2880, 2950, 3020, 3090, 3160, 3230, 3300, 3370,
  3440, 3510, 3580, 3650, 3720, 3790, 3860, 3930,
  4000, 4070
};

/* -----------------------------------------------
 *  PROTOTYPES
 * -----------------------------------------------
 */
void MyHandleNoteOn(byte channel, byte pitch, byte velocity);
void MyHandleNoteOff(byte channel, byte pitch, byte velocity);

/*void checkencoder();
//void updateLEDValue(unsigned int nibble,unsigned int updstate);
void updateLED();
void clearLED();
*/

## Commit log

2019-01-31 Project copied from MK1
2019-01-31 Schematic updated to MK2
2019-02-01 README.md - MK2 base idea description
2019-02-02 Kicad faliure - unknown state
2019-02-02 Footprints and MIDI out
2019-02-02 3D Models
2019-02-03 MIDI out simplified #1
2019-02-03 Initial PCB Layout MK2 - incomplete
2019-02-03 Footprint replace in sch, netlist and PCB
2019-02-03 Footprints and LED labels
2019-02-03 Jumper fixes
2019-02-03 Sch and PCB advancements
2019-02-03 RC output on CV
2019-02-03 Component replacement
2019-02-03 Routing....
2019-02-03 front routed....
2019-02-04 SCH added Rout for Gate3 and Gate4 Op Amp
2019-02-04 Initial PCB finished - no DRC
2019-02-04 GND plane
2019-02-04 Component text on PCB
2019-02-04 Gerber RevA
2019-02-04 gerber w extra pwr and zip - RevA
2019-02-05 Schematic
2019-02-05 BOM and A2 gerber (front silk minor)
2019-02-28 MOVED PINS AROUND ON ARDUINO
2019-02-28 pinout changed in PCB
2019-02-28 modify wiring - make new gerber
2019-03-23 Arduino initiated
2019-03-23 Update AJ_LFO_quad_out_CV1CV2.ino
    code compiling
2019-03-23 Tracking I2C missing audio
2019-04-18 Arduino - new project
2019-04-18 Gate working
    Gate working
2019-04-18 Remember last pitch before note off (monophonic)
2019-04-18 5 states initiated
2019-04-18 Blink indication for speed state
2019-04-21 Added Gate retrigger of node-on
